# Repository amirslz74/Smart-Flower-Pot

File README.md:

# Smart Flower Pot

An open-source ESP32 plant controller designed in EasyEDA, assembled, and tested at home for four years. This repository also provides an inspectable KiCad 10 conversion as a real EasyEDA-to-KiCad case study.

> **Status:** working prototype and reference design. The KiCad conversion preserves the source design, but imported ERC/DRC findings must be reviewed before a new manufacturing run. See [the migration audit](docs/EASYEDA_TO_KICAD.md).

## Highlights

- ESP32 Wi-Fi controller with two relay outputs
- DHT11 temperature and humidity monitoring
- Browser dashboard hosted on SPIFFS
- NTP time synchronization
- Original EasyEDA Standard JSON sources
- Editable KiCad 10 schematic and PCB
- Real assembly and long-term test photographs
- Machine-readable ERC/DRC reports and schematic PDF

## Gallery

| Operating controller | Home test | KiCad conversion |
| --- | --- | --- |
|  |  |  |

## Repository map

```text
firmware/esp32-web-controller/  Current firmware and web UI
firmware/examples/              Earlier reference experiment
Hardware/easyeda/               Original sources and previews
Hardware/kicad-10/              Editable KiCad 10 project
manufacturing/reports/          KiCad ERC and DRC results
docs/                           Guides and project photographs
```

## Quick start

1. Copy `firmware/esp32-web-controller/secrets.example.h` to `secrets.h`.
2. Add your Wi-Fi details; `secrets.h` is ignored by Git.
3. Install the ESP32 Arduino core, DHT library, and ESPAsyncWebServer dependencies.
4. Upload the `data` directory to SPIFFS, then flash `SmartFlowerPot.ino`.
5. Adjust the static network settings for your installation.

See [firmware instructions](docs/FIRMWARE.md) and the [hardware guide](docs/HARDWARE.md).

## EasyEDA and KiCad

The KiCad version was created with KiCad's native EasyEDA Standard importer, not redrawn from screenshots. The PCB import contains 71 footprints (including mounting-hole objects), 479 track segments, 48 vias, and two zones. After zone refill, KiCad reports zero unconnected PCB items.

Automatic conversion is not engineering sign-off. Imported library associations, symbol electrical types, silkscreen, courtyard, and design-rule conventions explain the recorded warnings. The reports remain visible so contributors can improve the conversion honestly.

## Safety

Relay contacts may carry dangerous voltages. This educational design has no certification. Disconnect power before handling it; use proper fusing, enclosure, strain relief, creepage, and clearance; and obtain qualified review for mains-voltage use.

## Contributing and license

Issues and pull requests are welcome; read [CONTRIBUTING.md](CONTRIBUTING.md). Hardware and manufacturing files use the strongly reciprocal [CERN-OHL-S-2.0](LICENSES/CERN-OHL-S-2.0.txt); firmware and documentation use the [MIT License](LICENSES/MIT.txt). See [LICENSE.md](LICENSE.md) for the scope of each license.

The early asynchronous web-server example retains its Random Nerd Tutorials attribution. Any original hardware project used as a basis must also be credited before release.

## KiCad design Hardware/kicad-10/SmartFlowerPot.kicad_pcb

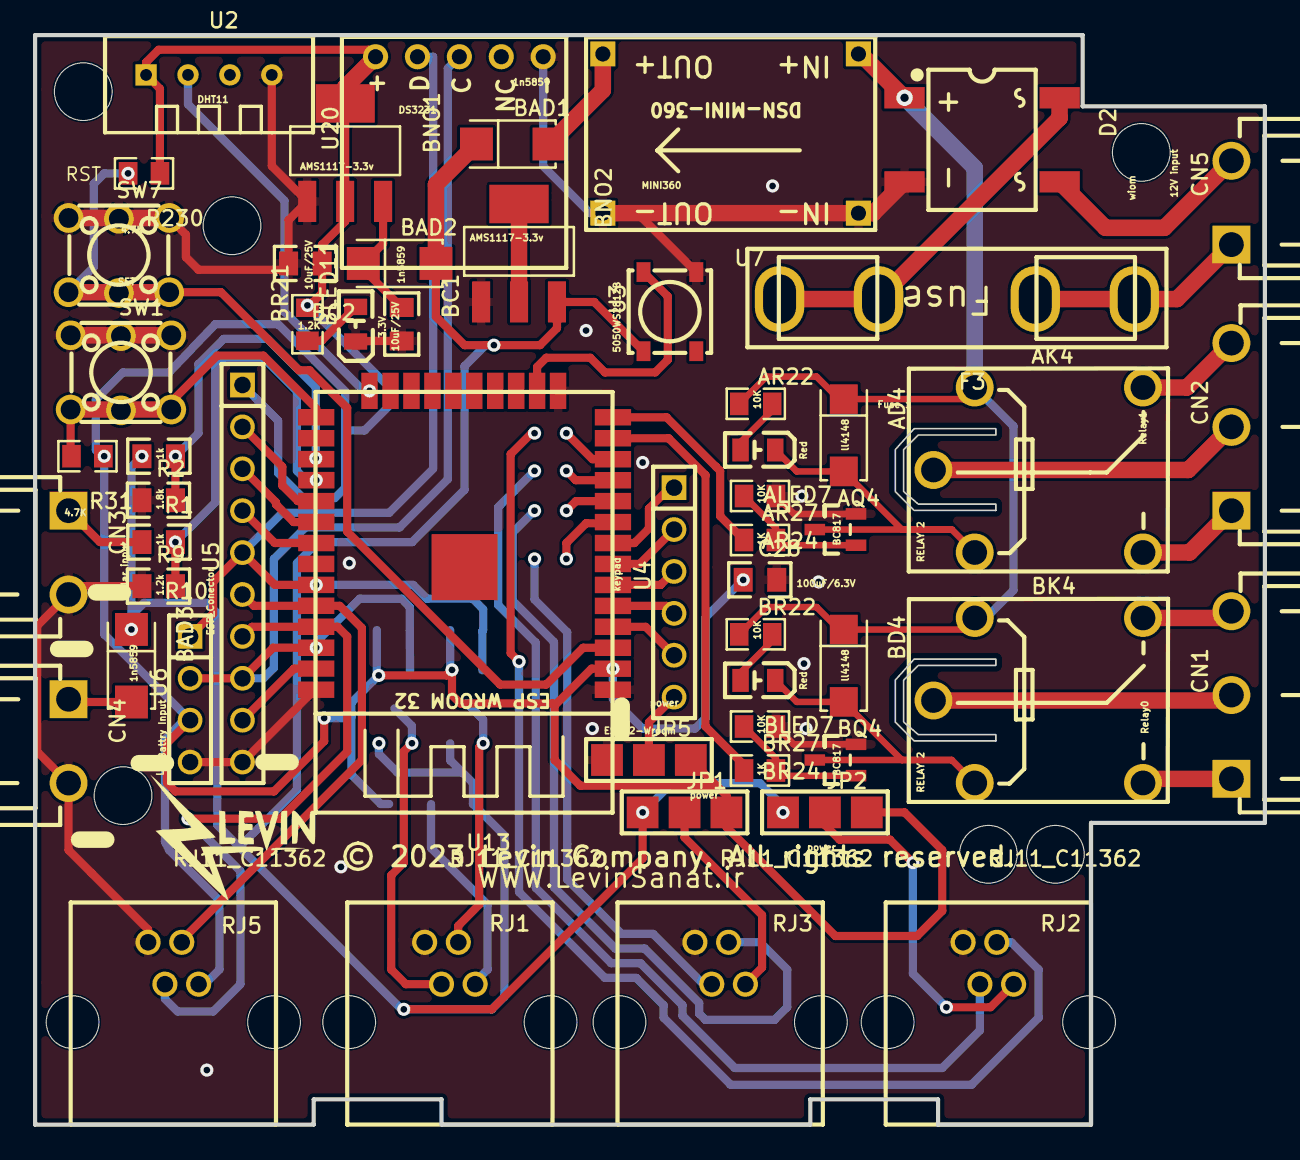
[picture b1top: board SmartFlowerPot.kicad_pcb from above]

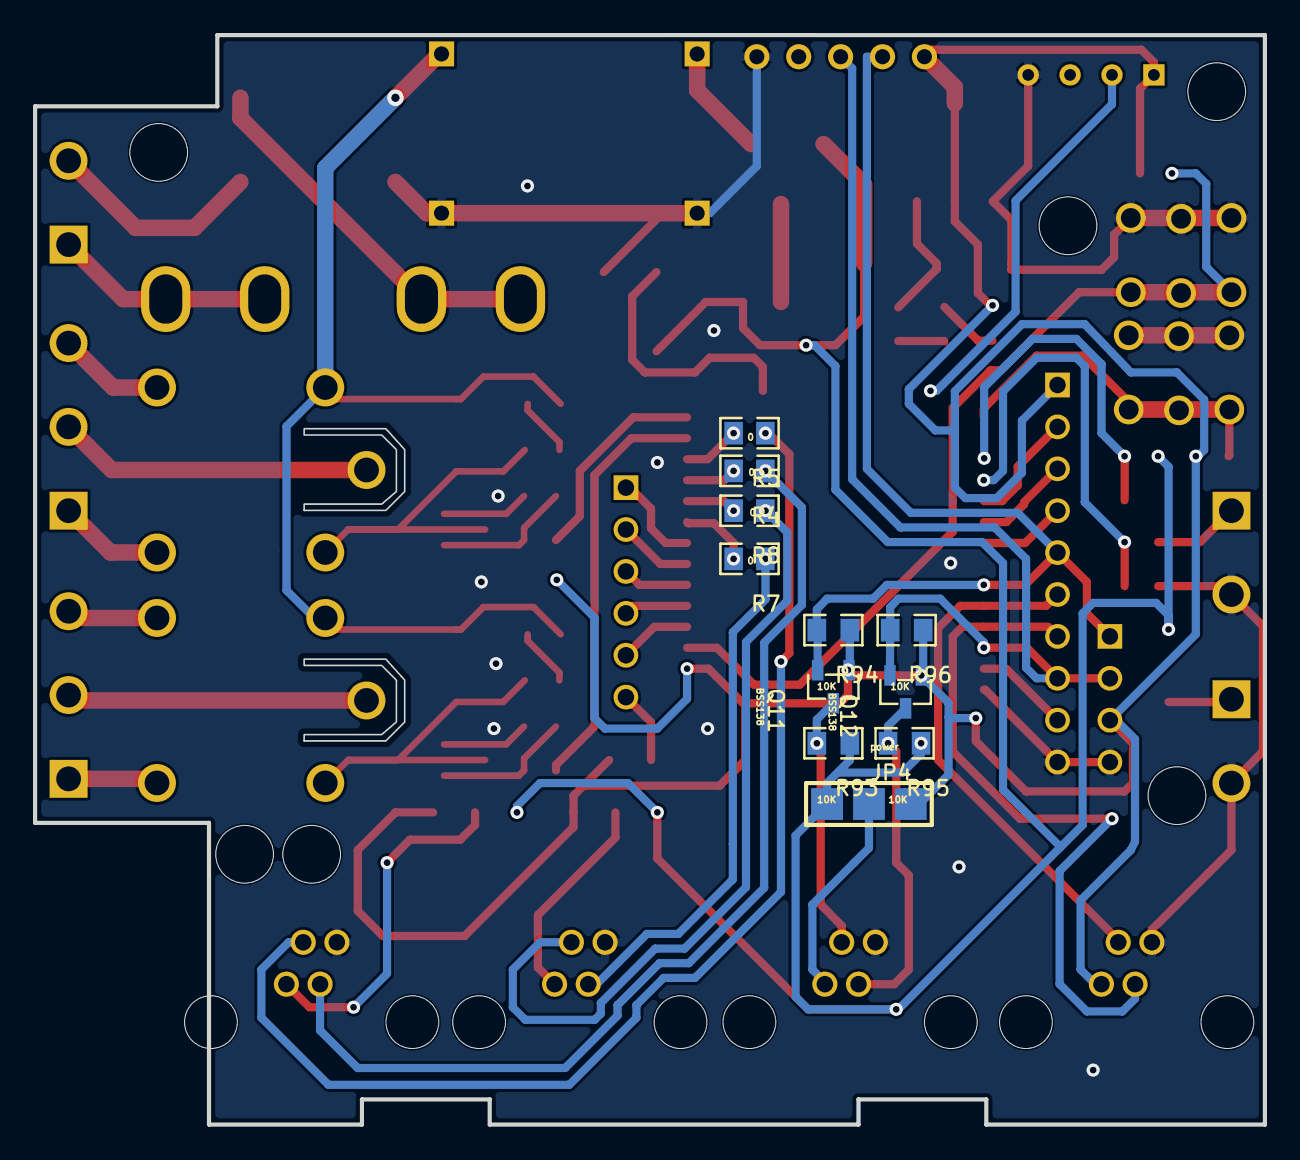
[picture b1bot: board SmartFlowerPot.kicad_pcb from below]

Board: 2 copper layers, 74.5 x 66.0 mm, 71 parts (11 on the bottom side), 60 nets.

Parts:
AD4: ll4148; SMA_L4.4-W2.6-LS5.0-RD
AK4: RELAY 2; RELAY BABY MILON HLS_T78
ALED7: Red; LED0805-R-RD
AQ4: BC817; SOT-23-3_L2.9-W1.3-P1.90-LS2.4-BR
AR22, AR24: 10K; R0805
AR27: 1K; R0805
BAD1, BAD2, BAD3: 1n5859; SMA_L4.3-W2.6-LS5.1-RD
BC1, BC2: 10uF/25V; 0805
BD4: ll4148; SMA_L4.4-W2.6-LS5.0-RD
BK4: RELAY 2; RELAY BABY MILON HLS_T78
BLED7: Red; LED0805-R-RD
BLED11: 3.3V; LED0805-R-RD
BNO1, BNO2: AMS1117-3.3v; SOT-223-3_L6.5-W3.4-P2.30-LS7.0-BR
BQ4: BC817; SOT-23-3_L2.9-W1.3-P1.90-LS2.4-BR
BR21: 1.2K; R0805
BR22, BR24: 10K; R0805
BR27: 1K; R0805
C28: 100uF/6.3V; 0805
CN1: Relay0; PHONIX 3PIN (5.08MM)
CN2: Relay1; PHONIX 3PIN (5.08MM)
CN3: Solar input; PHONIX 2PIN (5.08MM)
CN4: Battry Input; PHONIX 2PIN (5.08MM)
CN5: 12V input; PHONIX 2PIN (5.08MM)
D2: wiom; SDIP-4_L8.3-W6.4-P5.10-LS9.9-BL
F3: Fuse 1; FUSE
Hole_gge17519: Hole_gge17519
Hole_gge17534: Hole_gge17534
Hole_gge17549: Hole_gge17549
Hole_gge17624: Hole_gge17624
Hole_gge17639: Hole_gge17639
Hole_gge24158: Hole_gge24158
JP1, JP2, JP4, JP5: power; JUMPER 3X1 (PIN= 2.54)
Q11, Q12: BSS138; SOT-23-3_L2.9-W1.3-P1.90-LS2.4-BR
R1, R10: 1k; 0805
R2: 1.8k; 0805
R4, R5, R7, R8: 0; R0805
R9: 1.2k; 0805
R31, R230: 4.7K; R0805
R93, R94, R95, R96: 10K; R0805
RJ1, RJ2, RJ3, RJ5: RJ11_C11362; RJ11-TH_C11362
SW1: SET; SWITCH 4 PIN 6*6*6
SW7: RST; SWITCH 4 PIN 6*6*6
U2: DHT11; SENSOR-TH_DHT11
U3: 5050WS2812B; LED-SMD_5050WS2812B
U4: keypad; 1X6 HEADER (PIN = 2.54)
U5: ESP_Conector; 1X10 HEADER (PIN = 2.54)
U6: LCD; 1X4 HEADER (PIN = 2.54)
U7: MINI360; DSN-MINI-360
U13: ESP32-Wroom; ESP32_WROOM_FOOTPRINT
U20: DS3231

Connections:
0-COM: BK4.3, CN1.2
0-NC: BK4.4, CN1.1
0-NO: BK4.5, CN1.3
1-COM: AK4.3, CN2.2
1-NC: AK4.4, CN2.1
1-NO: AK4.5, CN2.3
+2.5V: BNO2.2, BNO2.4
+3.3V: BC2.1, BNO1.2, BNO1.4, BR21.2, C28.1, JP1.1, JP2.1, JP4.1, JP5.1, Q11.1, Q12.1, R31.1, R94.1, R96.1, R230.1, RJ5.1, U2.1, U5.1, U6.3, U13.2, U20.1
+5V: BAD1.1, BAD2.2, BAD3.1, BNO2.3, JP1.3, JP2.3, JP4.3, R1.2, R93.1, R95.1, U3.1
+12V: AD4.1, AK4.2, AR22.1, BD4.1, BK4.2, BR22.1, D2.1, U7.1
+SVCC: CN3.1, R10.2
AD4_2: AD4.2, AK4.1, ALED7.2, AQ4.3
ALED7_1: ALED7.1, AR22.2
AR27_2: AQ4.1, AR24.2, AR27.2
BD4_2: BD4.2, BK4.1, BLED7.2, BQ4.3
BLED7_1: BLED7.1, BR22.2
BNO1_3: BAD2.1, BC1.1, BNO1.3
BR21_1: BLED11.1, BR21.1
BR27_2: BQ4.1, BR24.2, BR27.2
CN4_1: BAD3.2, CN4.1
CS0: U5.2, U13.29
D2_3: CN5.2, D2.3
EN: R230.2, SW7.3, SW7.4, U13.3
F3_1: CN5.1, F3.1
F3_2: D2.4, F3.2
GND: AQ4.2, AR24.1, BC1.2, BC2.2, BLED11.2, BNO1.1, BNO2.1, BQ4.2, BR24.1, C28.2, CN3.2, CN4.2, D2.2, JP5.3, R2.1, R9.1, RJ1.4, RJ2.4, RJ3.4, RJ5.4, SW1.1, SW1.2, SW7.1, SW7.2, U2.4, U3.3, U5.10, U6.4, U7.2, U7.4, U13.1, U13.15, U13.38, U20.5
IO0: R31.2, SW1.3, SW1.4, U13.25
IO2: U2.2, U13.24
IO12: AR27.1, U13.14
IO13: U3.4, U13.16
IO14: BR27.1, U13.13
IO16: R1.1, R2.2, U13.27
IO17: R9.2, R10.1, U13.28
IO25: R8.2, U13.10
IO26: R4.2, U13.11
IO27: R5.2, U13.12
IO32: U4.1, U13.8
IO33: R7.2, U13.9
IO34: U4.3, U13.6
IO35: U4.2, U13.7
IO36: U4.5, U13.4
IO39: U4.4, U13.5
JP1_2: JP1.2, RJ3.1
JP2_2: JP2.2, RJ2.1
JP4_2: JP4.2, RJ1.1
MISO: U5.4, U13.31
MOSI: U5.9, U13.37
R4_1: R4.1, RJ2.3
R5_1: R5.1, RJ2.2
R7_1: R7.1, RJ3.3
R8_1: R8.1, RJ3.2
RXD0: RJ5.2, U5.6, U13.34
SCL: Q12.2, R96.2, U5.8, U6.2, U13.36, U20.3
SCL(H): Q12.3, R95.2, RJ1.3
SCLK: U5.3, U13.30
SDA: Q11.2, R94.2, U5.5, U6.1, U13.33, U20.2
SDA(H): Q11.3, R93.2, RJ1.2
TXD0: RJ5.3, U5.7, U13.35
U4_6: JP5.2, U4.6
U7_3: BAD1.2, U7.3

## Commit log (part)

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2023-11-15 2 Relay done
2023-11-15 aded dht first code
2023-11-17 make foldering

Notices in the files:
Hardware/kicad-10/SmartFlowerPot.kicad_pcb:
© 2023 Levin Company. All rights reserved.
